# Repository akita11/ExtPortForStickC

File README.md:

# ExtPortForStickC

[M5StickCPlus](https://www.switch-science.com/products/6470)や[M5StickCPlus2](https://www.switch-science.com/products/9350)の上部コネクタに接続し、最大2つのGroveポートを増設することができます。

M5StickCPlusの上部コネクタに出ているI/Oポートは数が少ないため、配線を切り替えて使用できるようになっています。

## ピン配置

2つのGroveポートがあり、それぞれのピン配置は以下のとおりです。

- PortB（黒）: G25/G26/V/G
- PortC（青）: G26/[G0 or G25]/V/G

PortCの2番ピンは、コネクタ横のショートピンによって、G0またはG25を切り替えることができます。（中央-"G0"側をショート=G0、中央-"G25"側をショート=G25）

※M5StickCPlus/2の仕様として、G25はG36と内部で接続されています。このピンはアナログ入力として使用できるG36を使うこともできますが、その場合はG25を入力ピンとして設定して使用してください。

## Author

Junichi Akita (@akita11) / akita@ifdl.jp

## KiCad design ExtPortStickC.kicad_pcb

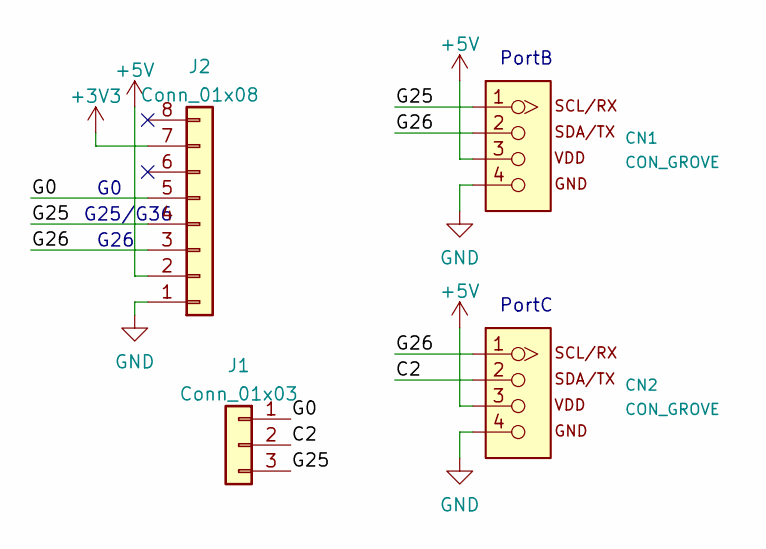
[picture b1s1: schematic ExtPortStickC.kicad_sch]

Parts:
CN1, CN2: CON_GROVE; CON_GROVE_H_roundPad
J1: Conn_01x03; PinHeader_1x03_P2.54mm_Vertical
J2: Conn_01x08; PinHeader_1x08_P2.54mm_Horizontal

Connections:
+3V3: J2.7
+5V: CN1.3, CN2.3, J2.2
/C2: CN2.2, J1.2
/G0: J1.1, J2.5
/G25: CN1.1, J1.3, J2.4
/G26: CN1.2, CN2.1, J2.3
GND: CN1.4, CN2.4, J2.1

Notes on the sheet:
G25/G36
G26
PortC
PortB

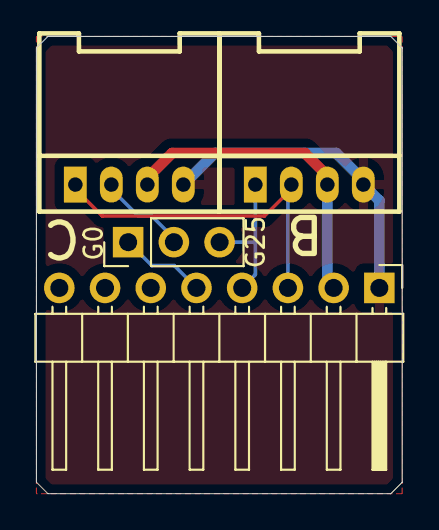
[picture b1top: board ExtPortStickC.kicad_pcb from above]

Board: 2 copper layers, 20.3 x 25.4 mm, 4 parts (0 on the bottom side), 6 nets.

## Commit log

2025-04-23 add photo & readme
